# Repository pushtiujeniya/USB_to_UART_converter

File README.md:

# USB_to_UART_converter
-----------------------
USB to UART converter module convert USB data to UART using FT232RL IC.

# Hardware components used
--------------------------
- FT232RL (28 pin package) from FTDI
- 3 pin connector for USB bus power with  selectable external supply so one can select the supply between 3.3V or 5V DC
- Ferrite bead
- 2 smd led for TX and RX data transmission indication
- 6 pin MCU connector
- USB-B (USB TYPE-B) USB 2.0 Receptacle Connector 4 Position Through Hole 
- resistors
- capacitors

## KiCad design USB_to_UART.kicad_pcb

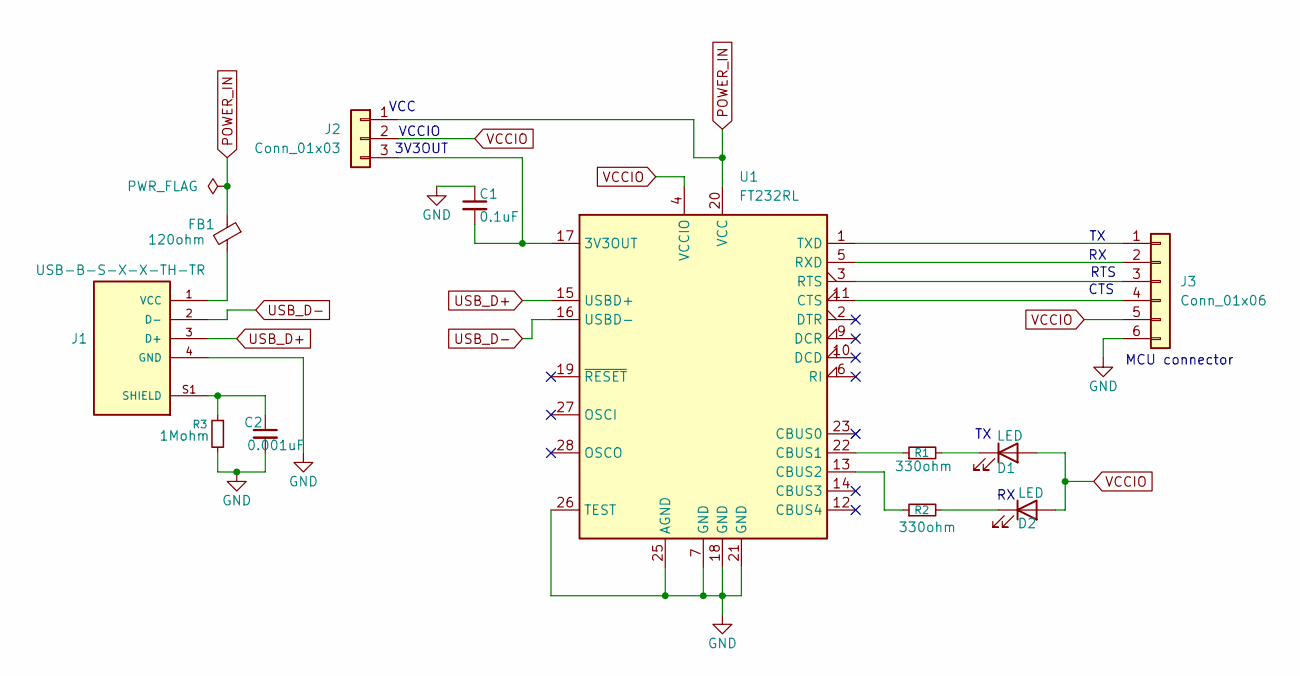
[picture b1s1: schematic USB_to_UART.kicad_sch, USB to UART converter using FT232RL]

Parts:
C1: 0.1uF; C_0603_1608Metric
C2: 0.001uF; C_0603_1608Metric
D1, D2: LED; LED_0805_2012Metric
FB1: 120ohm; LairdTech_28C0236-0JW-10
J1: USB-B-S-X-X-TH-TR; SAMTEC_USB-B-S-X-X-TH-TR; PARTREV Q
J2: Conn_01x03; PinHeader_1x03_P2.54mm_Vertical
J3: Conn_01x06; PinHeader_1x06_P2.54mm_Horizontal
R1, R2: 330ohm; R_0603_1608Metric
R3: 1Mohm; R_0603_1608Metric
U1: FT232RL; SSOP-28_5.3x10.2mm_P0.65mm

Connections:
GND: C1.1, C2.2, J1.4 (GND), J3.6, R3.2, U1.7 (GND), U1.18 (GND), U1.21 (GND), U1.25 (AGND), U1.26 (TEST)
unnamed: C2.1, J1.S1 (SHIELD), J1.S2 (SHIELD), R3.1
unnamed: D1.1 (K), R1.2
unnamed: D2.1 (K), R2.2
unnamed: FB1.2, J1.1 (VCC)
unnamed: C1.2, J2.3, U1.17 (3V3OUT)
unnamed: J3.1, U1.1 (TXD)
unnamed: J3.2, U1.5 (RXD)
unnamed: J3.3, U1.3 (RTS)
unnamed: J3.4, U1.11 (CTS)
unnamed: R1.1, U1.22 (CBUS1)
unnamed: R2.1, U1.13 (CBUS2)
POWER_IN: FB1.1, J2.1, U1.20 (VCC)
USB_D+: J1.3 (D+), U1.15 (USBD+)
USB_D-: J1.2 (D-), U1.16 (USBD-)
VCCIO: D1.2 (A), D2.2 (A), J2.2, J3.5, U1.4 (VCCIO)

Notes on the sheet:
VCCIO
CTS
RTS
VCC
MCU connector
3V3OUT

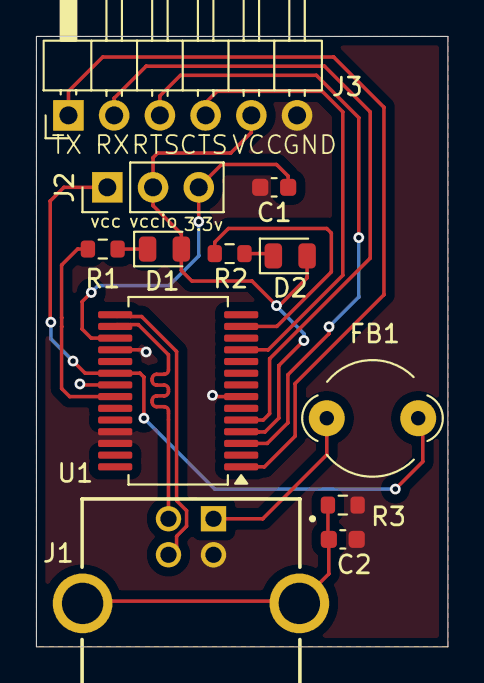
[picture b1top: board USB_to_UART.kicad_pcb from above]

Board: 2 copper layers, 22.9 x 33.9 mm, 12 parts (0 on the bottom side), 16 nets.

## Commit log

2026-04-04 temp file
2026-04-04 3d view images added
2026-04-04 schematic and all layout pdf added
2026-04-04 schematic file added
2026-04-04 layout file added
2026-04-04 usb to uart pro files
2026-04-04 external library files added
2026-04-04 Add temp file to External library directory
2026-04-04 external library files added
2026-04-04 Update README with USB to UART converter details
    Added detailed description of the USB to UART converter and its hardware components.
2026-04-04 Update README with USB-B connector details
2026-05-07 USB to UART converter document
